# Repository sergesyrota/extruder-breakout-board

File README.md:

# extruder-breakout-board
Extruder motor board with connectors to other components for 3d printer.

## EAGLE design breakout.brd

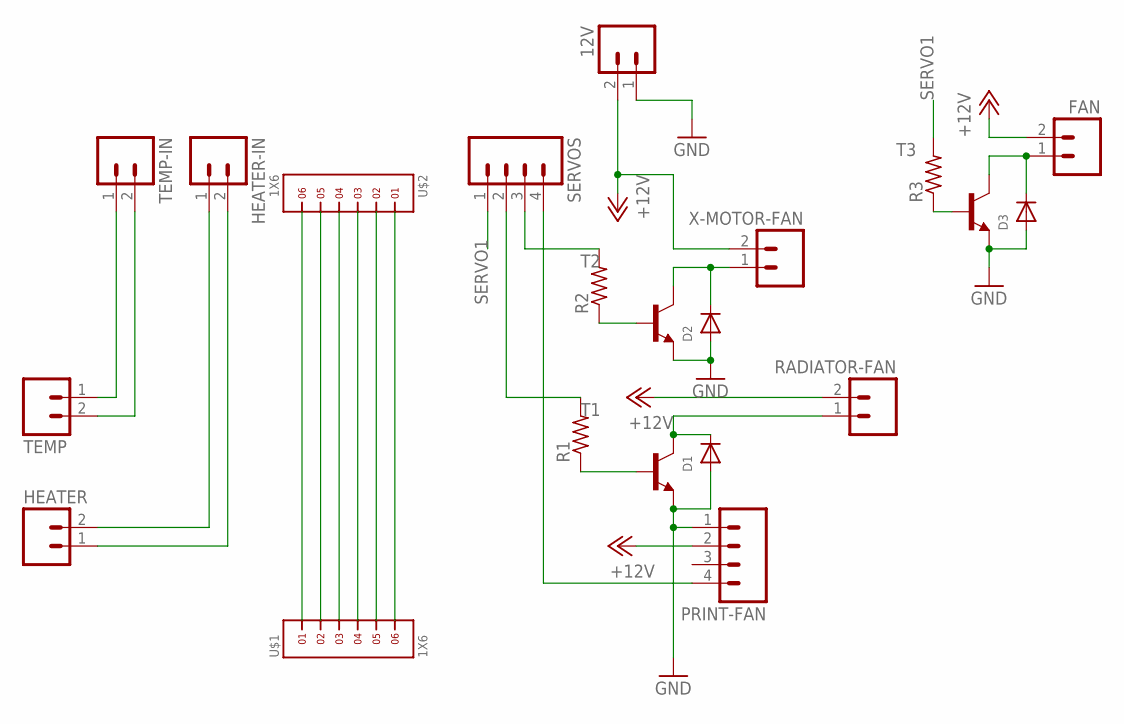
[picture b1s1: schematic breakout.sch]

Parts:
12V: M02; 02P
D1, D2, D3: DIODESMA; SMADIODE
FAN: M02; 02P
HEATER: M02; 02P
HEATER-IN: M02; 02P
PRINT-FAN: M04; 04P
R1, R2, R3: R-US_R0603; R0603
RADIATOR-FAN: M02; 02P
SERVOS: M04; 04P
T1, T2, T3: BC808-NPN-SOT23-BEC; SOT23-BEC
TEMP: M02; 02P
TEMP-IN: M02; 02P
U$1, U$2: 1X6
X-MOTOR-FAN: M02; 02P

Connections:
+12V: 12V.2, FAN.2, PRINT-FAN.2, RADIATOR-FAN.2, X-MOTOR-FAN.2
GND: 12V.1, D1.A, D2.A, D3.A, PRINT-FAN.1, T1.E, T2.E, T3.E
unnamed: U$1.1, U$2.6
unnamed: U$1.2, U$2.5
unnamed: U$1.3, U$2.4
unnamed: U$1.4, U$2.3
unnamed: U$1.5, U$2.2
unnamed: U$1.6, U$2.1
unnamed: PRINT-FAN.4, SERVOS.4
unnamed: TEMP.1, TEMP-IN.1
unnamed: TEMP.2, TEMP-IN.2
unnamed: HEATER.2, HEATER-IN.1
unnamed: HEATER.1, HEATER-IN.2
unnamed: D1.C, RADIATOR-FAN.1, T1.C
unnamed: D3.C, FAN.1, T3.C
unnamed: R1.1, T1.B
unnamed: R1.2, SERVOS.2
unnamed: D2.C, T2.C, X-MOTOR-FAN.1
unnamed: R3.1, T3.B
unnamed: R2.1, T2.B
unnamed: R2.2, SERVOS.3
SERVO1: R3.2, SERVOS.1

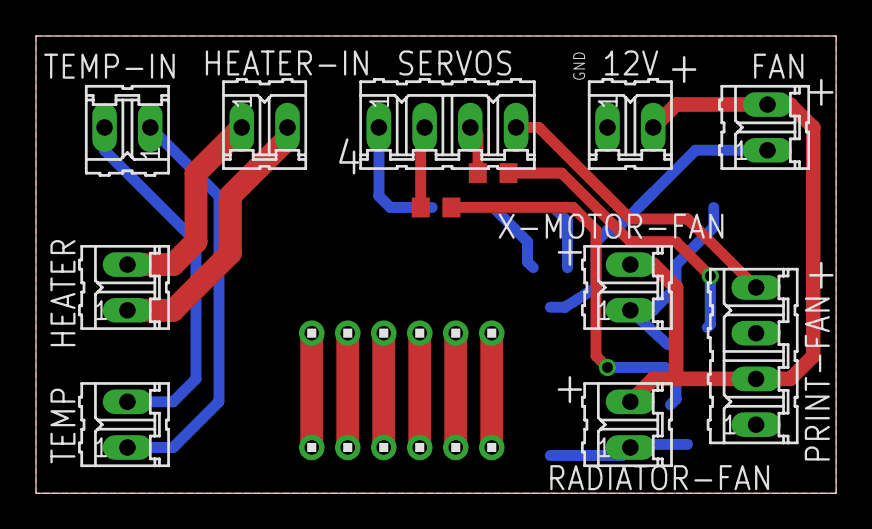
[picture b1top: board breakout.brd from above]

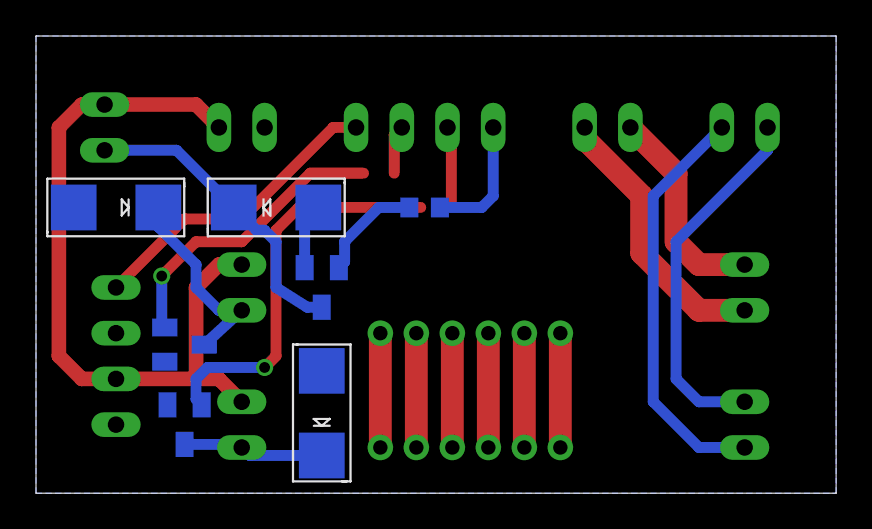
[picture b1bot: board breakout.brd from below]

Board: 2 copper layers, 44.5 x 25.4 mm, 21 parts (7 on the bottom side), 22 nets.

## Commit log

2019-01-21 Initial version with incorrect conenctor
2019-01-21 Adjusted to 2mm spacing for motor connector, and moved some connectors a bit.
2019-01-22 Adjusting labels and positioning.
